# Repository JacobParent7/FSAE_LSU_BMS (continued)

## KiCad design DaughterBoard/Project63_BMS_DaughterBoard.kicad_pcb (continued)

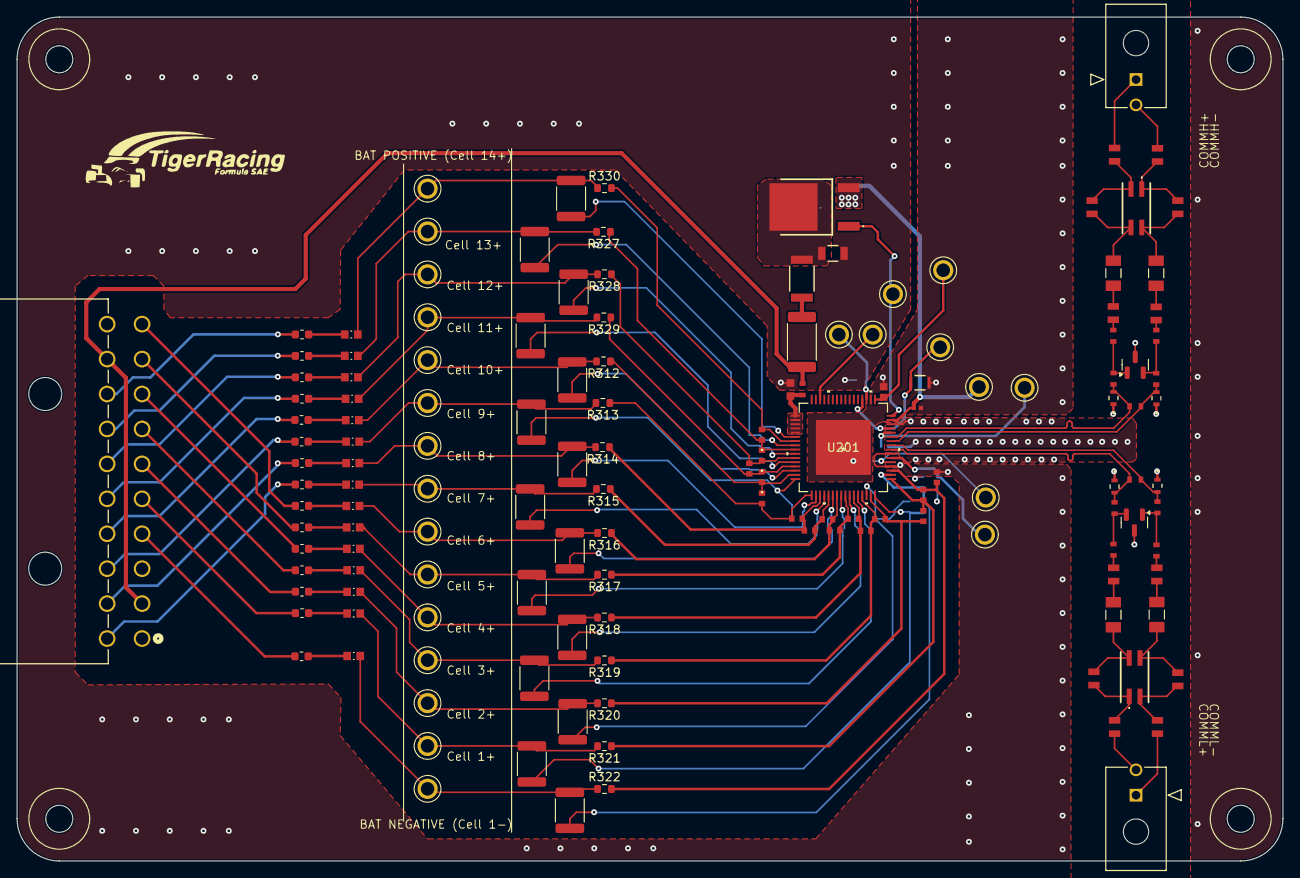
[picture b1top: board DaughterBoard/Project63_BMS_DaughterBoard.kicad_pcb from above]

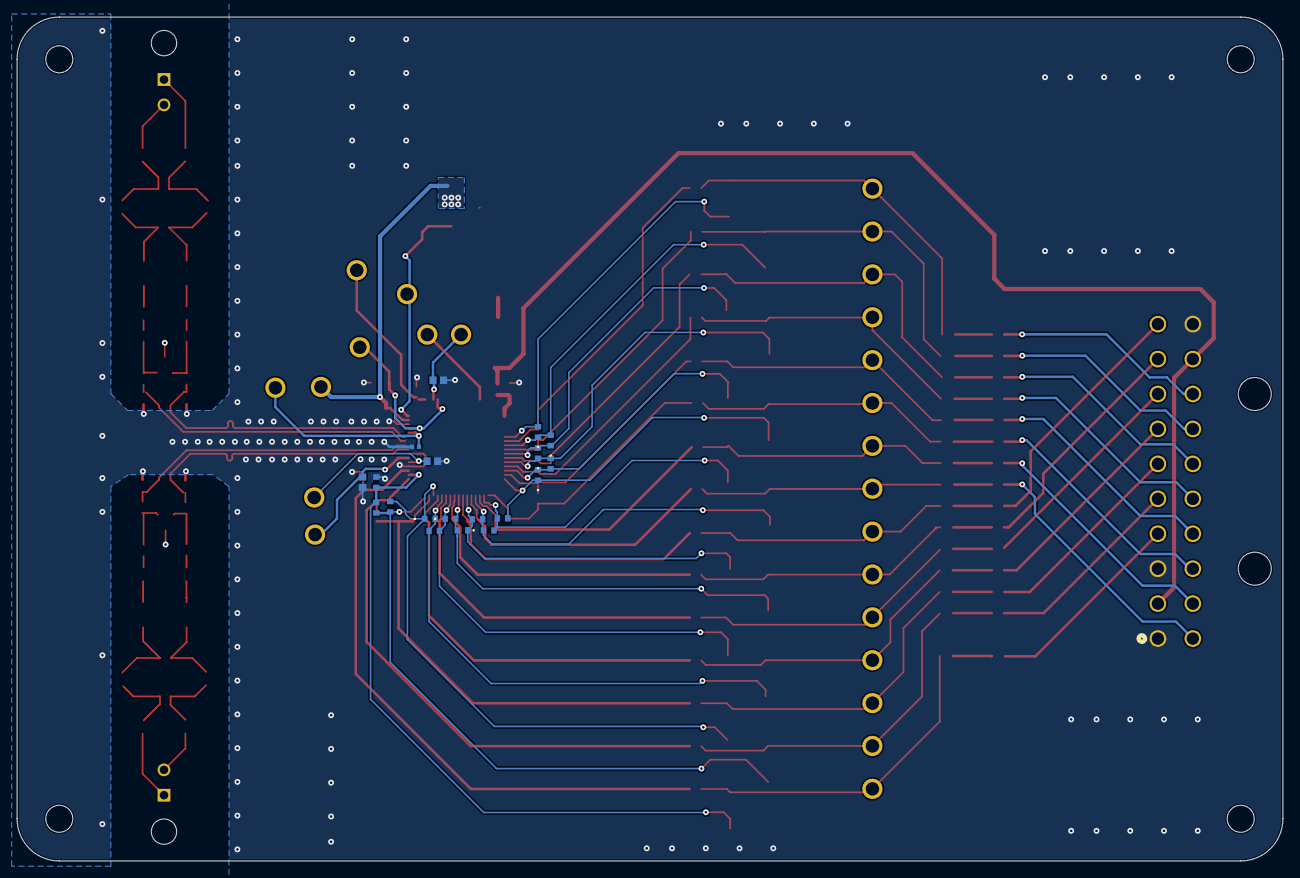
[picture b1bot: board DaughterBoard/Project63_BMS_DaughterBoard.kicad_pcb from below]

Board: 4 copper layers, 150.0 x 100.0 mm, 169 parts (19 on the bottom side), 117 nets.

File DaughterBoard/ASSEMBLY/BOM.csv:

"Reference","Value","Footprint","JLC PCB Part #"
"C201","10nF","GCM188R72A103KA37J:CAPC1608X90N","C2167085"
"C202,C208","0.1uF","GCM155R71A104KA55D:CAP_GCM15_1p05X0p55X0p55_MUR-L","C161163"
"C203,C204,C205,C207","1uF","C0603C105K8RACAUTO:CAPC18095_95N_KEM-L","C29936"
"C206","4.7uF","C2012X7R1A475M125AC:CAP_2012_TDK-L","C277499"
"C301,C302,C303,C304,C305,C306,C307,C308,C309,C310,C311,C312,C313,C314,C315,C316,C317,C318,C319,C320,C321,C322,C323,C324,C325,C326,C327,C328,C329,C330","0.47uF","GCM188R71C474KA55D:G-188_MUR-L","C161214"
"C601","0.22uF","GCM31MR72A224KA37L:G-31_MUR-L","C161277"
"C701,C702,C707,C708","2200pF","1206J2K00222KXR (1):CAPC3216X160N","C107194"
"C703,C704,C705,C706","220pF","CL10B221JB8NNNC:CAP_CL10_SAM-L","C107081"
"D701,D702","24V","Package_TO_SOT_SMD:SOT-23","C314266"
"F301,F302,F303,F304,F305,F306,F307,F308,F309,F310,F311,F323,F324,F325,F326","0438.250WRA","Fuse:Fuse_0603_1608Metric","C151137"
"F312,F313,F314,F315,F316,F317,F318,F319,F320,F321,F322,F327,F328,F329,F330","0686F1000-01","0686F1000-01:FUSC1608X60N","C136329"
"FL701,FL702","470uH","KiCad:744242471","C488250"
"Q601","ZXTN4004KTC","ZXTN4004KTC:ZXTN4004KTC","C157603"
"R201","30","ERJ-3EKF30R0V:RC0603N_PAN-L","C403150"
"R301,R302,R303,R304,R305,R306,R307,R308,R309,R310,R311,R323,R324,R325,R326","7.5","Resistor_SMD:R_1812_4532Metric","C5204035"
"R312,R313,R314,R315,R316,R317,R318,R319,R320,R321,R322,R327,R328,R329,R330","100","Resistor_SMD:R_0603_1608Metric","C5123580"
"R601","100","CRCW2010100RFKEF:RES_CRCW_2010-L","C305269"
"R602","200","Resistor_SMD:R_2512_6332Metric","C2935248"
"R701,R702,R705,R706,R709,R710,R713,R714,R715,R716,R721,R722","0","CRCW08050000Z0EAHP:RES_CRCW_0805_VIS-L","C844811"
"R703,R704,R719,R720","0","RC0603JR-070RL:RC0603N_YAG-L","C95177"
"R707,R708,R717,R718","51","CRCW060351R0JNEA:RC0603N_VIS-L","C844178"
"R711,R712","1k","ERJ-3EKF1001V:RC0603N_PAN-L","C2907002"
"U201","BQ79614PAPRQ1","BQ79614:QFP_4PAPRQ1_TEX-L","C3682338"

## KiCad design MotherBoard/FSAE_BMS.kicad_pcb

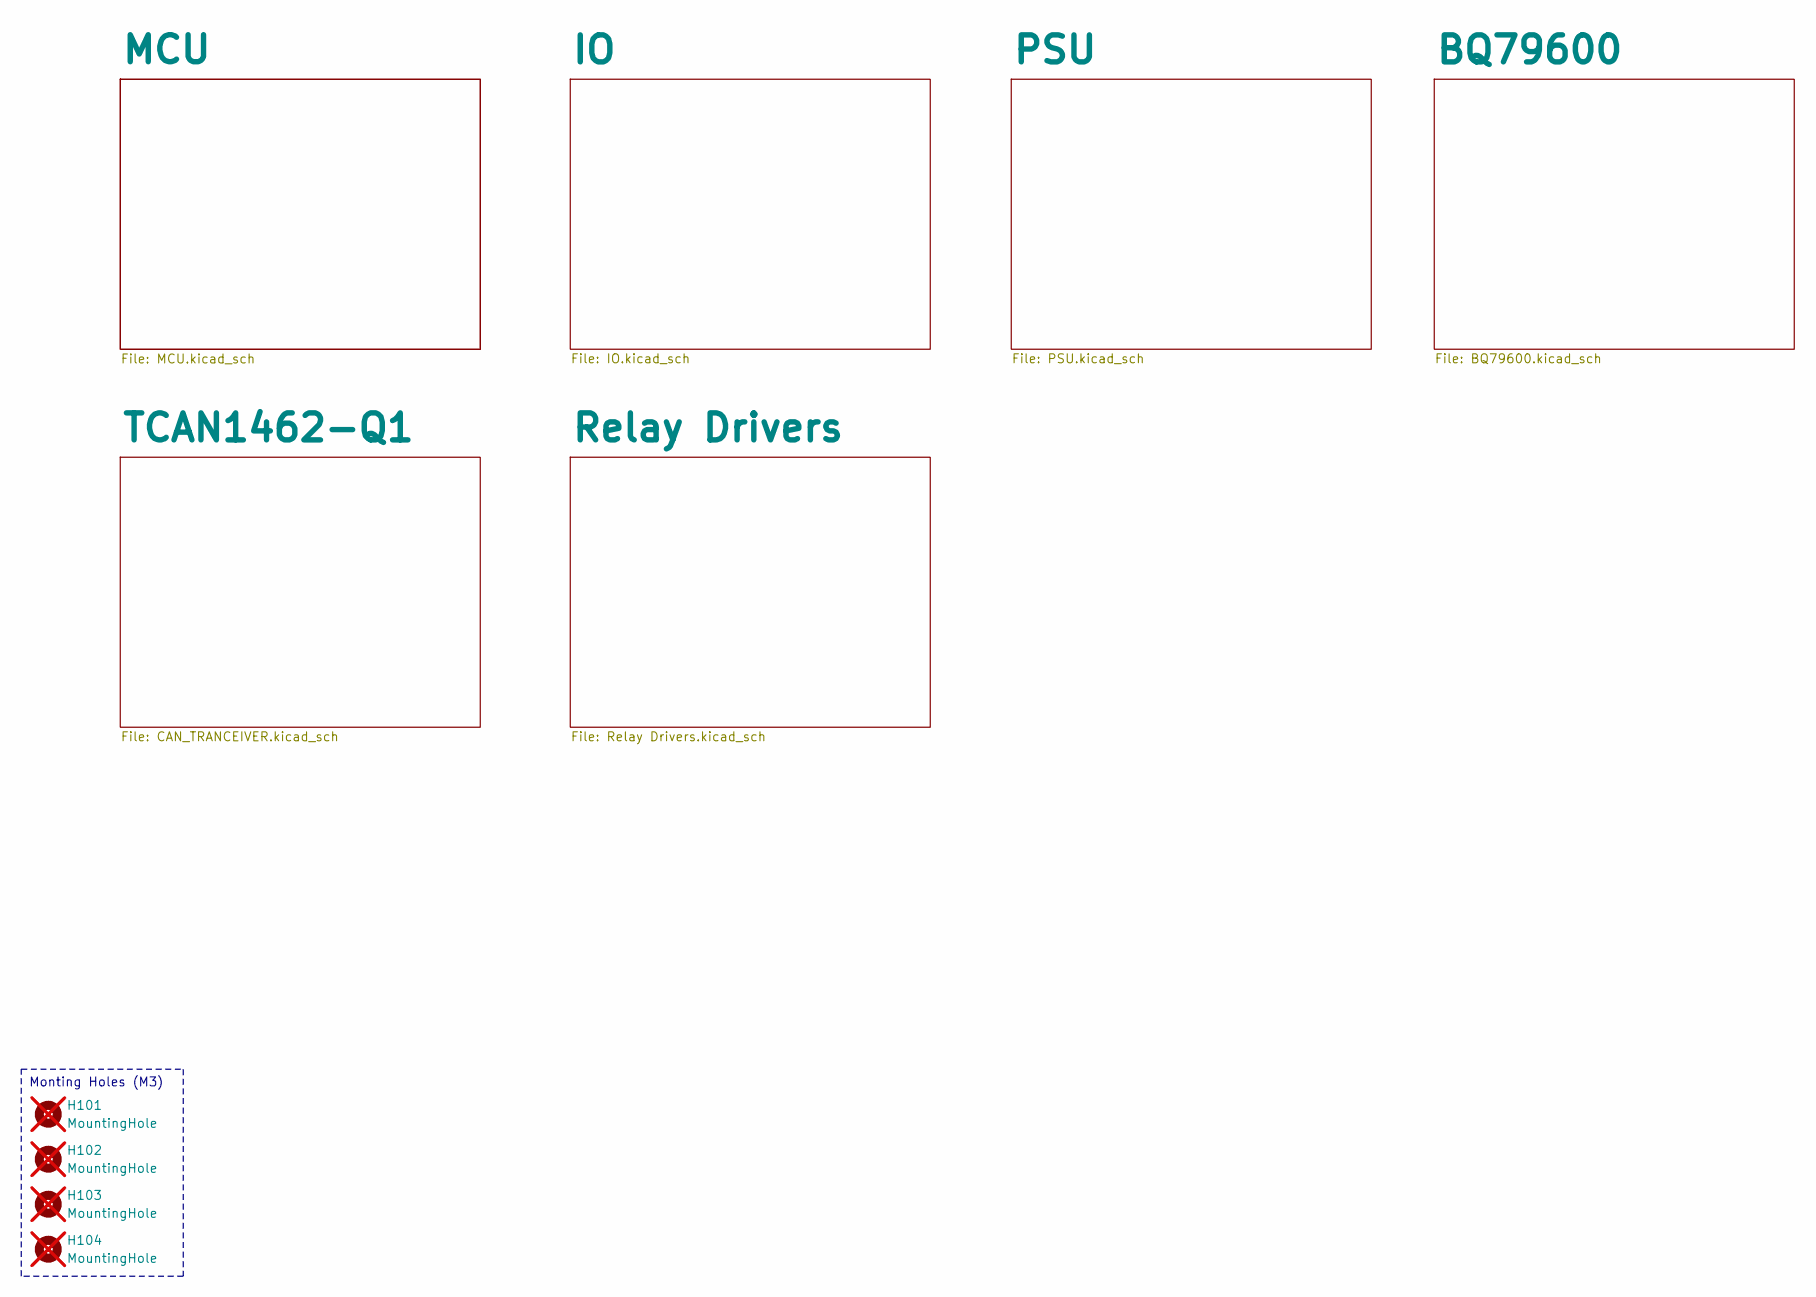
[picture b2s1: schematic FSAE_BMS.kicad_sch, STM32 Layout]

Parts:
H101, H102, H103, H104: MountingHole; MountingHole_3.2mm_M3; not fitted

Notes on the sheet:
Monting Holes (M3)

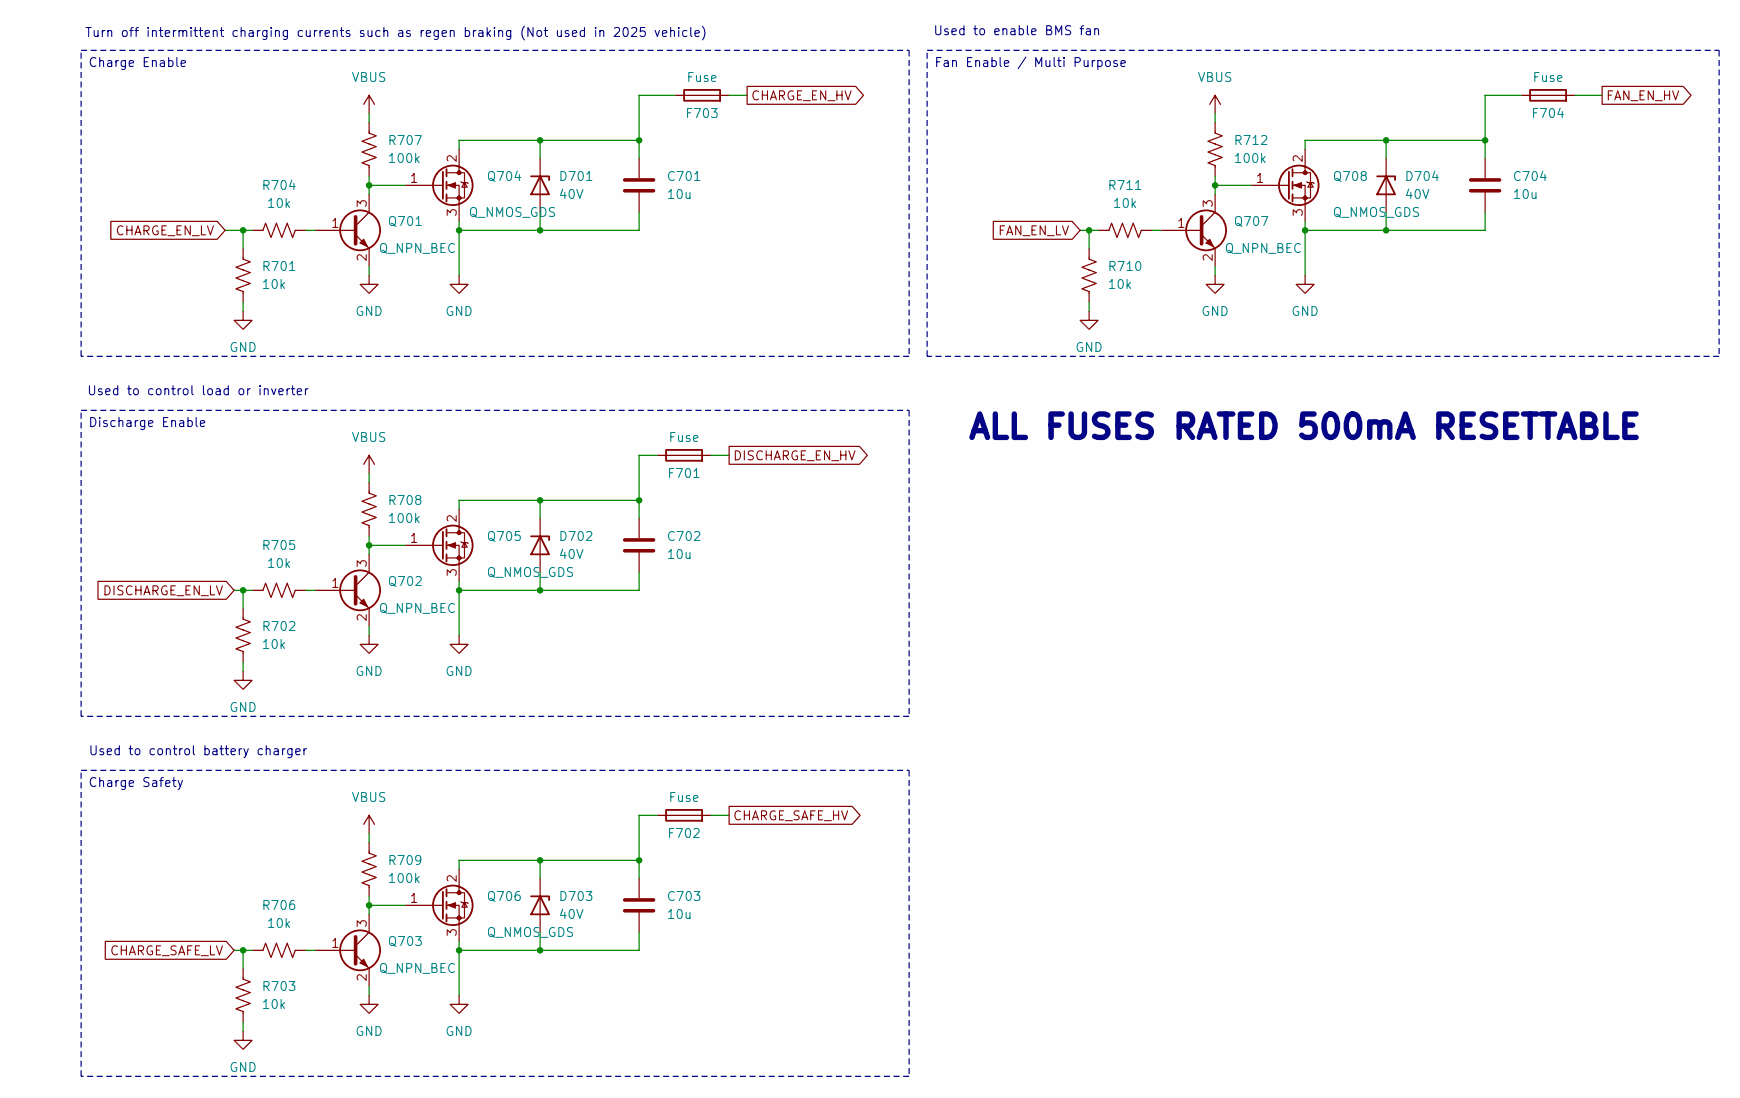
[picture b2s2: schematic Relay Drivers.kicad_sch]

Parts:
C701, C702, C703, C704: 10u; C_1206_3216Metric; Manufacturer_Part_Number CL31A106KBHNNNE; JLCPCB Part # C13585
D701, D702, D703, D704: 40V; D_SOD-123; Manufacturer_Part_Number BZT52C30; JLCPCB Part # C19077418
F701, F702, F703, F704: Fuse; Fuse_1812_4532Metric; Manufacturer_Part_Number SMD1812P050TF/30; JLCPCB Part # C12559
Q701, Q702, Q703, Q707: Q_NPN_BEC; SOT-23; Manufacturer_Part_Number MMBT3904; JLCPCB Part # C7420353
Q704, Q705, Q706, Q708: Q_NMOS_GDS; TO-263-2; Manufacturer_Part_Number IRF3205STRLPBF; JLCPCB Part # C2613
R701, R702, R703, R704, R705, R706, R710, R711: 10k; R_0402_1005Metric; Manufacturer_Part_Number FRC0603J103TS; JLCPCB Part # C2930027
R707, R708, R709, R712: 100k; R_0402_1005Metric; Manufacturer_Part_Number 0402WGF1003TCE; JLCPCB Part # C25741

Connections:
CHARGE_EN_HV: F703.2; also elsewhere on the board
CHARGE_EN_LV: R701.2, R704.1; also elsewhere on the board
CHARGE_SAFE_HV: F702.2; also elsewhere on the board
CHARGE_SAFE_LV: R703.2, R706.1; also elsewhere on the board
DISCHARGE_EN_HV: F701.2; also elsewhere on the board
DISCHARGE_EN_LV: R702.2, R705.1; also elsewhere on the board
FAN_EN_HV: F704.2; also elsewhere on the board
FAN_EN_LV: R710.2, R711.1; also elsewhere on the board
GND: C701.2, C702.2, C703.2, C704.2, D701.2 (A), D702.2 (A), D703.2 (A), D704.2 (A), Q701.2 (E), Q702.2 (E), Q703.2 (E), Q704.3 (S), Q705.3 (S), Q706.3 (S), Q707.2 (E), Q708.3 (S), R701.1, R702.1, R703.1, R710.1; also elsewhere on the board
unnamed: C701.1, D701.1 (K), F703.1, Q704.2 (D)
unnamed: C702.1, D702.1 (K), F701.1, Q705.2 (D)
unnamed: C703.1, D703.1 (K), F702.1, Q706.2 (D)
unnamed: C704.1, D704.1 (K), F704.1, Q708.2 (D)
unnamed: Q701.1 (B), R704.2
unnamed: Q701.3 (C), Q704.1 (G), R707.2
unnamed: Q702.1 (B), R705.2
unnamed: Q702.3 (C), Q705.1 (G), R708.2
unnamed: Q703.1 (B), R706.2
unnamed: Q703.3 (C), Q706.1 (G), R709.2
unnamed: Q707.1 (B), R711.2
unnamed: Q707.3 (C), Q708.1 (G), R712.2
VBUS: R707.1, R708.1, R709.1, R712.1; also elsewhere on the board

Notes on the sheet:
Turn off intermittent charging currents such as regen braking (Not used in 2025 vehicle)
Used to control load or inverter
ALL FUSES RATED 500mA RESETTABLE
Used to control battery charger
Used to enable BMS fan
Charge Safety
Fan Enable / Multi Purpose
Discharge Enable
Charge Enable

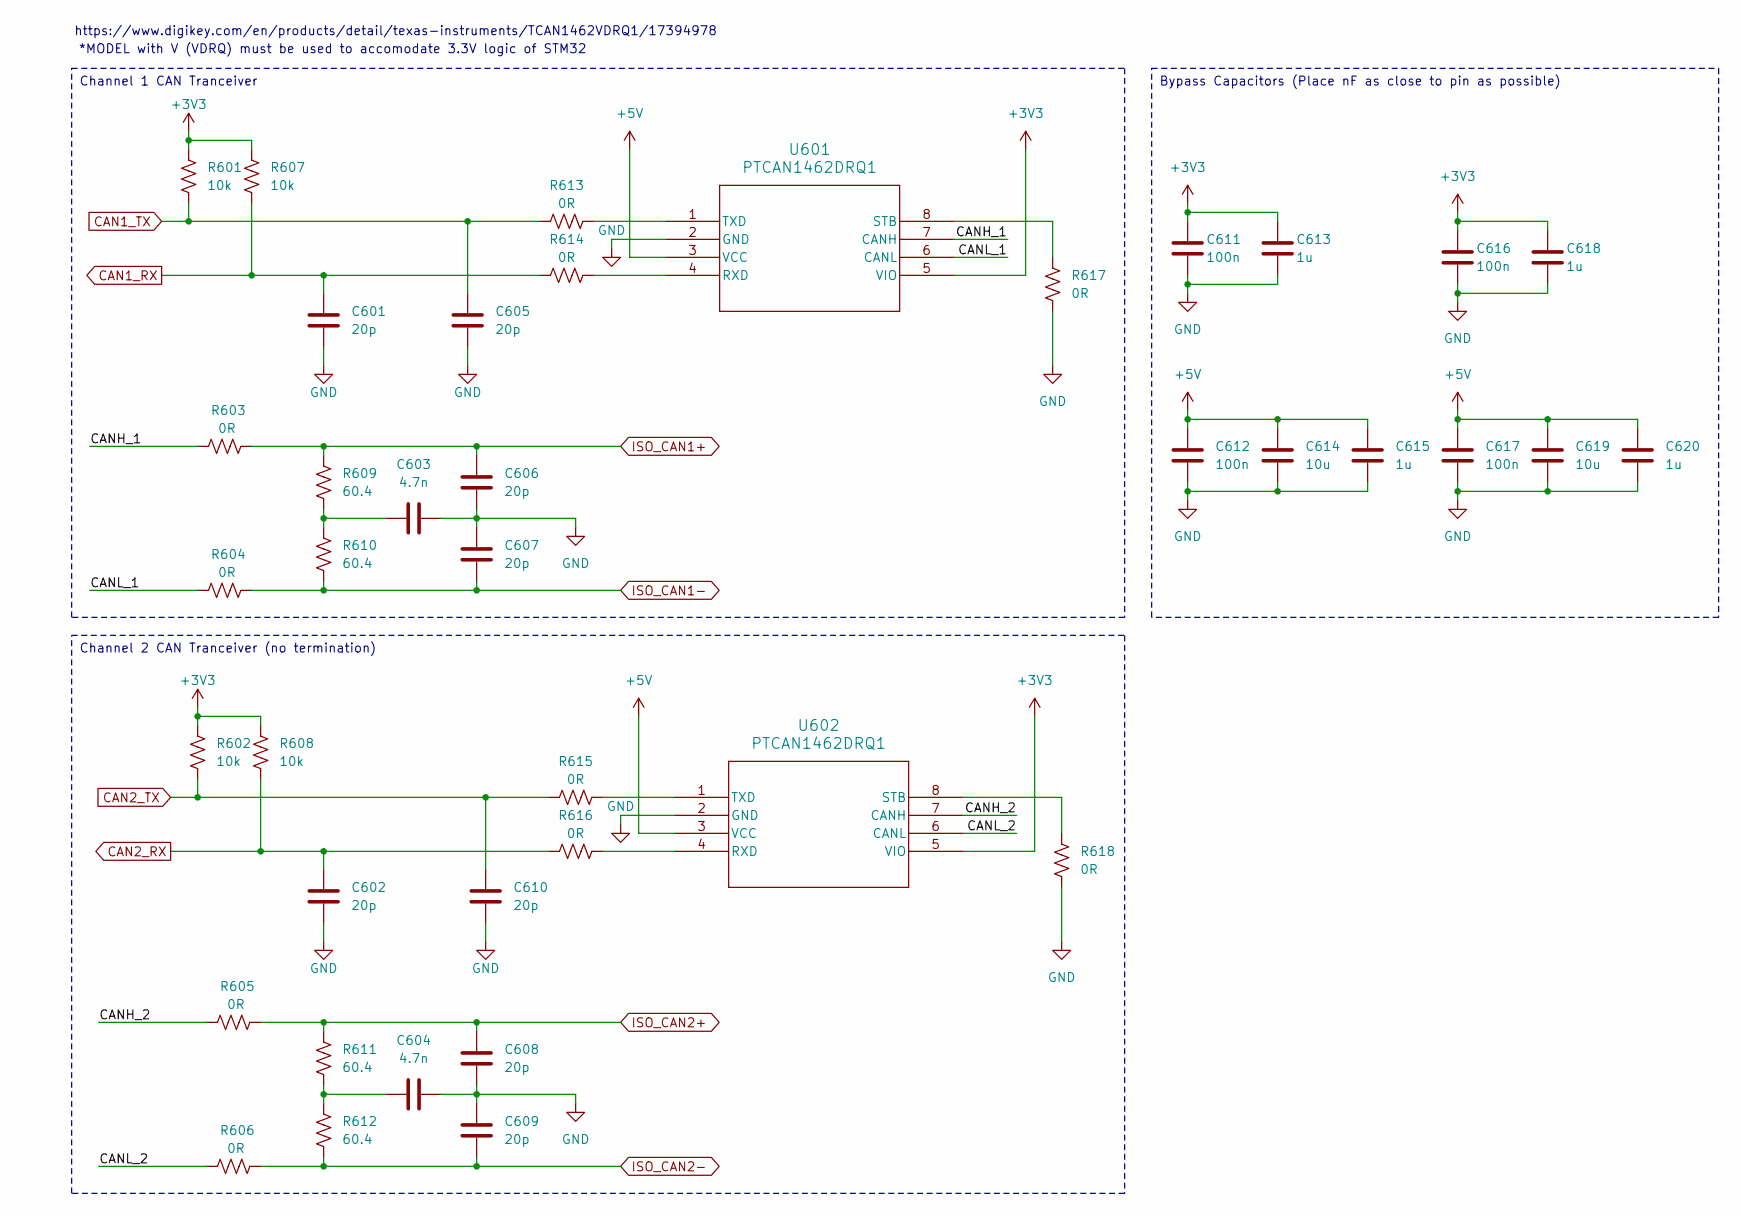
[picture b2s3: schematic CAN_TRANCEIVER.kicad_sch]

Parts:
C601, C602, C605, C606, C607, C608, C609, C610: 20p; C_0402_1005Metric; Manufacturer_Part_Number 0402CG200J500NT; JLCPCB Part # C1554
C603, C604: 4.7n; C_0402_1005Metric; Manufacturer_Part_Number CC0402JRX7R9BB472; JLCPCB Part # C281757
C611, C612, C616, C617: 100n; C_0402_1005Metric; Manufacturer_Part_Number CL05B104KO5NNNC; JLCPCB Part # C1525
C613, C615, C618, C620: 1u; C_0402_1005Metric; Manufacturer_Part_Number CL05A105KO5NNNC; JLCPCB Part # C29266
C614, C619: 10u; C_0603_1608Metric; Manufacturer_Part_Number CL10A106KP8NNNC; JLCPCB Part # C19702
R601, R602, R607, R608: 10k; R_0402_1005Metric; Manufacturer_Part_Number FRC0603J103TS; JLCPCB Part # C2930027
R603, R604, R605, R606: 0R; R_1206_3216Metric; Manufacturer_Part_Number HP06W2J0000T5E; JLCPCB Part # C473612
R609, R610, R611, R612: 60.4; R_1210_3225Metric; Manufacturer_Part_Number AC1210FR-0760R4L; JLCPCB Part # C230306
R613, R614, R615, R616, R617, R618: 0R; R_0805_2012Metric; Manufacturer_Part_Number 0805W8F0000T5E; JLCPCB Part # C17477
U601, U602: PTCAN1462DRQ1; CAN1462; Manufacturer_Part_Number TCAN1462VDRQ1; JLCPCB Part # C7399456

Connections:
+3V3: C611.1, C613.1, C616.1, C618.1, R601.1, R602.1, R607.1, R608.1, U601.5 (VIO), U602.5 (VIO); also elsewhere on the board
+5V: C612.1, C614.1, C615.1, C617.1, C619.1, C620.1, U601.3 (VCC), U602.3 (VCC); also elsewhere on the board
/TCAN1462-Q1/CANH_1: R603.1, U601.7 (CANH)
/TCAN1462-Q1/CANH_2: R605.1, U602.7 (CANH)
/TCAN1462-Q1/CANL_1: R604.1, U601.6 (CANL)
/TCAN1462-Q1/CANL_2: R606.1, U602.6 (CANL)
CAN1_RX: C601.2, R607.2, R614.1; also elsewhere on the board
CAN1_TX: C605.2, R601.2, R613.1; also elsewhere on the board
CAN2_RX: C602.2, R608.2, R616.1; also elsewhere on the board
CAN2_TX: C610.2, R602.2, R615.1; also elsewhere on the board
GND: C601.1, C602.1, C603.2, C604.2, C605.1, C606.1, C607.2, C608.1, C609.2, C610.1, C611.2, C612.2, C613.2, C614.2, C615.2, C616.2, C617.2, C618.2, C619.2, C620.2, R617.2, R618.2, U601.2 (GND), U602.2 (GND); also elsewhere on the board
ISO_CAN1+: C606.2, R603.2, R609.2; also elsewhere on the board
ISO_CAN1-: C607.1, R604.2, R610.1; also elsewhere on the board
ISO_CAN2+: C608.2, R605.2, R611.2; also elsewhere on the board
ISO_CAN2-: C609.1, R606.2, R612.1; also elsewhere on the board
unnamed: C603.1, R609.1, R610.2
unnamed: C604.1, R611.1, R612.2
unnamed: R614.2, U601.4 (RXD)
unnamed: R617.1, U601.8 (STB)
unnamed: R613.2, U601.1 (TXD)
unnamed: R616.2, U602.4 (RXD)
unnamed: R618.1, U602.8 (STB)
unnamed: R615.2, U602.1 (TXD)

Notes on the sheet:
Channel 2 CAN Tranceiver (no termination)
Channel 1 CAN Tranceiver
Bypass Capacitors (Place nF as close to pin as possible)
https://www.digikey.com/en/products/detail/texas-instruments/TCAN1462VDRQ1/17394978
*MODEL with V (VDRQ) must be used to accomodate 3.3V logic of STM32

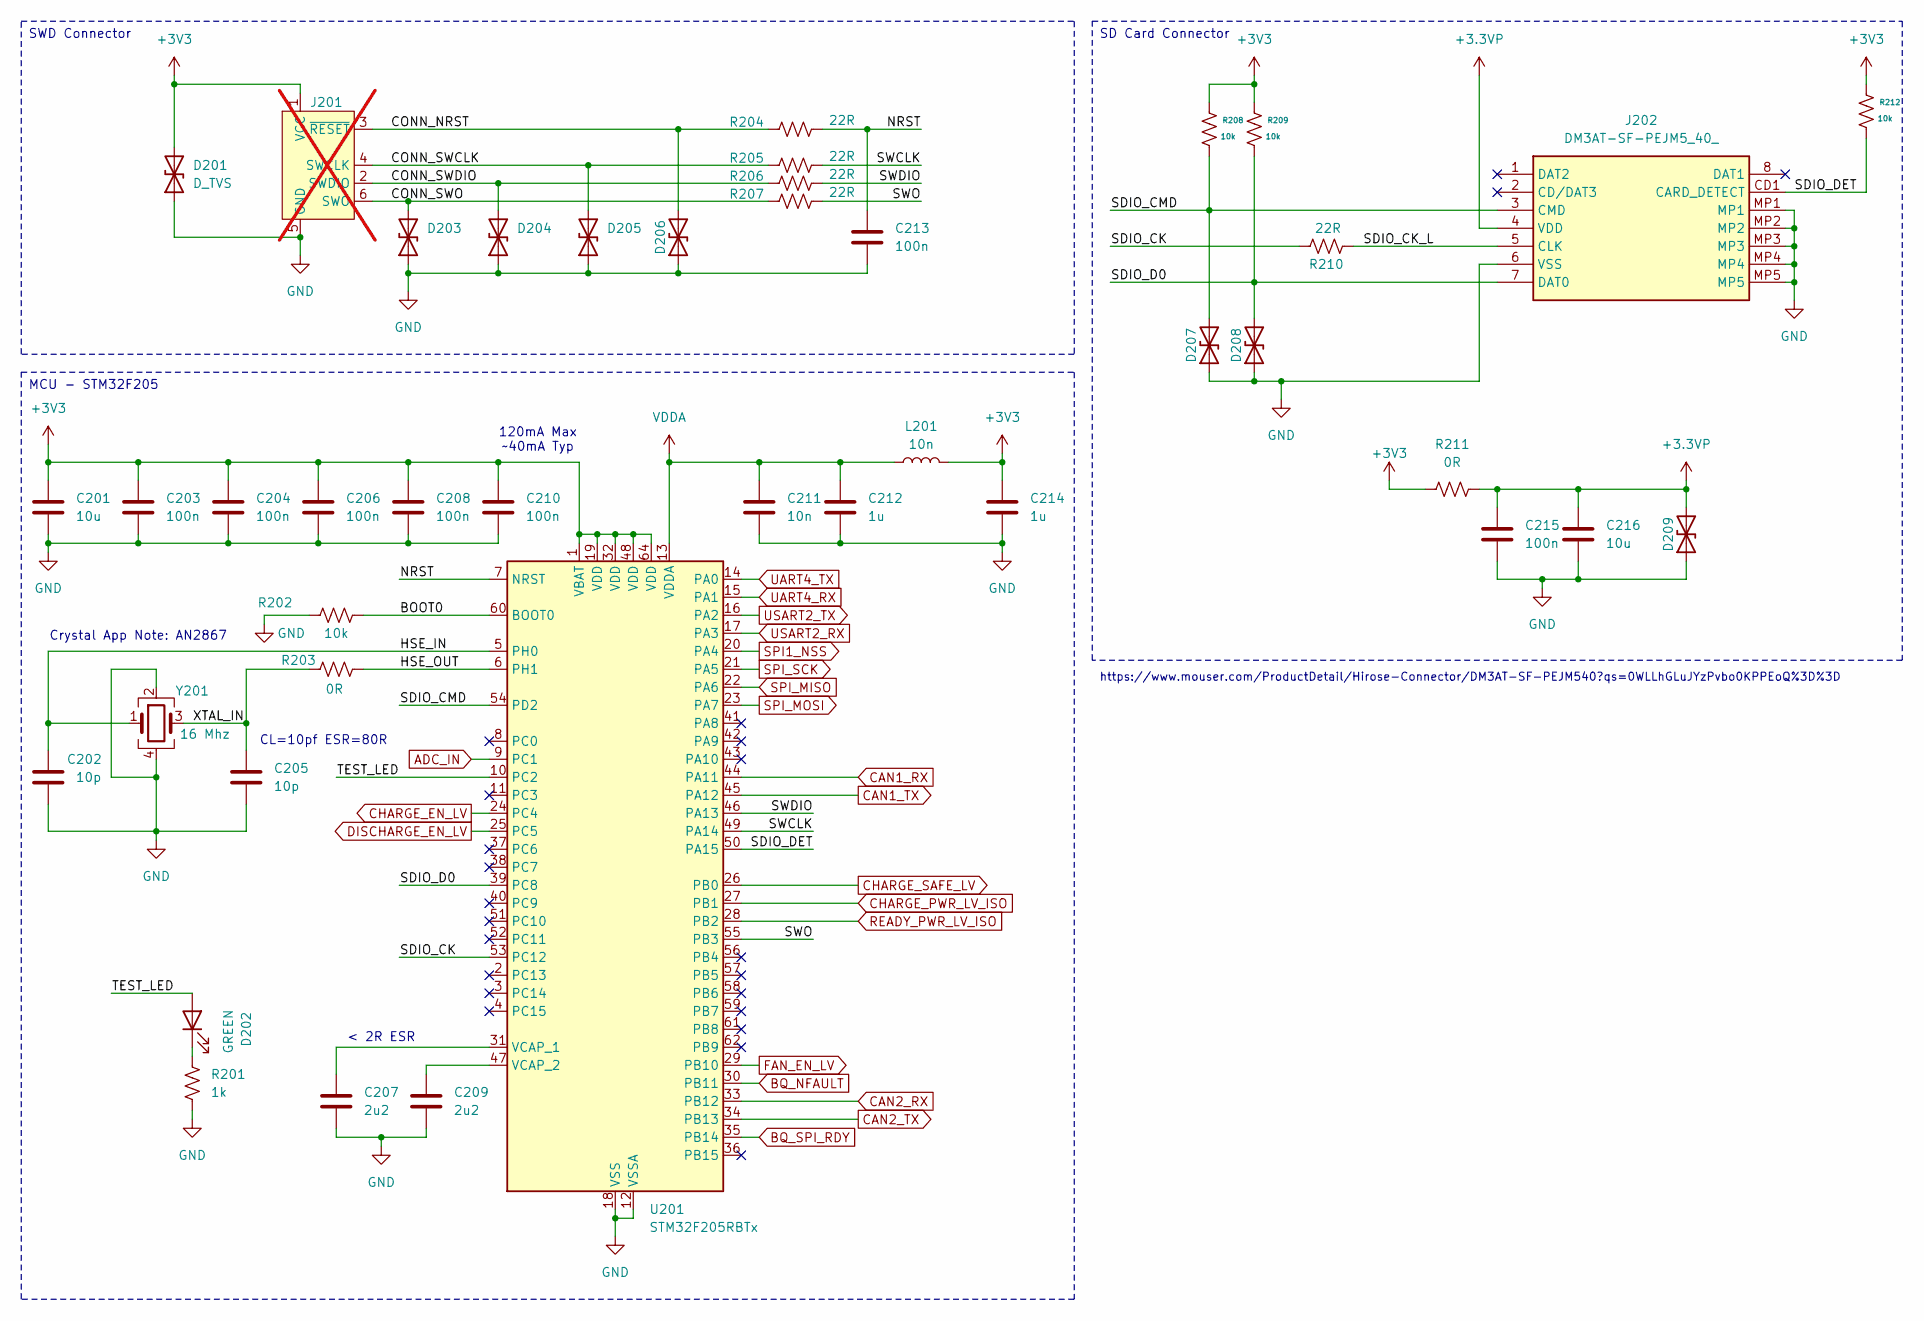
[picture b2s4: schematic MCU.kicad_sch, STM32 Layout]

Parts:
C201, C216: 10u; C_0603_1608Metric; Manufacturer_Part_Number CL10A106KP8NNNC; JLCPCB Part # C19702
C202, C205: 10p; C_0402_1005Metric; Manufacturer_Part_Number GRM1555C1H100FA01D; JLCPCB Part # C161520
C203, C204, C206, C208, C210, C213, C215: 100n; C_0402_1005Metric; Manufacturer_Part_Number CL05B104KO5NNNC; JLCPCB Part # C1525
C207, C209: 2u2; C_0603_1608Metric; Manufacturer_Part_Number 0603B225K250NT; JLCPCB Part # C99228
C211: 10n; C_0402_1005Metric; Manufacturer_Part_Number CC0402KRX7R9BB103; JLCPCB Part # C60133
C212, C214: 1u; C_0402_1005Metric; Manufacturer_Part_Number CL05A105KO5NNNC; JLCPCB Part # C29266
D201, D203, D204, D205, D206, D207, D208, D209: D_TVS; D_SOD-323; Manufacturer_Part_Number PESD3V3L1BA,115; JLCPCB Part # C51450
D202: GREEN; LED_0603_1608Metric; Manufacturer_Part_Number VLMTG1401-GS08; JLCPCB Part # C511604
J201: Conn_ARM_SWD_TagConnect_TC2030; Tag-Connect_TC2030-IDC-FP_2x03_P1.27mm_Vertical; not fitted
J202: DM3AT-SF-PEJM5_40_; SD_CARD; Mouser Part Number 798-DM3AT-SF-PEJM540
L201: 10n; L_0402_1005Metric; Manufacturer_Part_Number LQG15HN10NJ02D; JLCPCB Part # C21585
R201: 1k; R_0402_1005Metric; Manufacturer_Part_Number 0402WGF1001TCE; JLCPCB Part # C11702
R202, R208, R209, R212: 10k; R_0402_1005Metric; Manufacturer_Part_Number FRC0603J103TS; JLCPCB Part # C2930027
R203: 0R; R_0402_1005Metric; Manufacturer_Part_Number 0402WGF0000TCE; JLCPCB Part # C17168
R204, R205, R206, R207, R210: 22R; R_0402_1005Metric; Manufacturer_Part_Number 0402WGF220JTCE; JLCPCB Part # C25092
R211: 0R; R_2512_6332Metric; Manufacturer_Part_Number 25121WJ0000T4E; JLCPCB Part # C25469
U201: STM32F205RBTx; LQFP-64_10x10mm_P0.5mm; Manufacturer_Part_Number STM32F205RBT6; JLCPCB Part # C8364
Y201: 16 Mhz; Crystal_SMD_3225-4Pin_3.2x2.5mm; Manufacturer_Part_Number X322516MLB4SI; JLCPCB Part # C13738

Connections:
+3.3VP: C215.1, C216.1, D209.2 (A2), J202.4 (VDD), R211.2
+3V3: C201.1, C203.1, C204.1, C206.1, C208.1, C210.1, C214.1, D201.2 (A2), J201.1 (VCC), L201.2, R208.1, R209.1, R211.1, R212.1, U201.1 (VBAT), U201.19 (VDD), U201.32 (VDD), U201.48 (VDD), U201.64 (VDD); also elsewhere on the board
/MCU/BOOT0: R202.1, U201.60 (BOOT0)
/MCU/CONN_NRST: D206.2 (A2), J201.3 (~RESET), R204.1
/MCU/CONN_SWCLK: D205.2 (A2), J201.4 (SWCLK), R205.1
/MCU/CONN_SWDIO: D204.2 (A2), J201.2 (SWDIO), R206.1
/MCU/CONN_SWO: D203.2 (A2), J201.6 (SWO), R207.1
/MCU/HSE_IN: C202.1, U201.5 (PH0), Y201.1
/MCU/HSE_OUT: R203.2, U201.6 (PH1)
/MCU/NRST: C213.1, R204.2, U201.7 (NRST)
/MCU/SDIO_CK: R210.1, U201.53 (PC12)
/MCU/SDIO_CK_L: J202.5 (CLK), R210.2
/MCU/SDIO_CMD: D207.2 (A2), J202.3 (CMD), R208.2, U201.54 (PD2)
/MCU/SDIO_D0: D208.2 (A2), J202.7 (DAT0), R209.2, U201.39 (PC8)
/MCU/SDIO_DET: J202.CD1 (CARD_DETECT), R212.2, U201.50 (PA15)
/MCU/SWCLK: R205.2, U201.49 (PA14)
/MCU/SWDIO: R206.2, U201.46 (PA13)
/MCU/SWO: R207.2, U201.55 (PB3)
/MCU/TEST_LED: D202.2 (A), U201.10 (PC2)
/MCU/XTAL_IN: C205.1, R203.1, Y201.3
ADC_IN: U201.9 (PC1); also elsewhere on the board
BQ_NFAULT: U201.30 (PB11); also elsewhere on the board
BQ_SPI_RDY: U201.35 (PB14); also elsewhere on the board
CAN1_RX: U201.44 (PA11); also elsewhere on the board
CAN1_TX: U201.45 (PA12); also elsewhere on the board
CAN2_RX: U201.33 (PB12); also elsewhere on the board
CAN2_TX: U201.34 (PB13); also elsewhere on the board
CHARGE_EN_LV: U201.24 (PC4); also elsewhere on the board
CHARGE_PWR_LV_ISO: U201.27 (PB1); also elsewhere on the board
CHARGE_SAFE_LV: U201.26 (PB0); also elsewhere on the board
DISCHARGE_EN_LV: U201.25 (PC5); also elsewhere on the board
FAN_EN_LV: U201.29 (PB10); also elsewhere on the board
GND: C201.2, C202.2, C203.2, C204.2, C205.2, C206.2, C207.2, C208.2, C209.2, C210.2, C211.2, C212.2, C213.2, C214.2, C215.2, C216.2, D201.1 (A1), D203.1 (A1), D204.1 (A1), D205.1 (A1), D206.1 (A1), D207.1 (A1), D208.1 (A1), D209.1 (A1), J201.5 (GND), J202.6 (VSS), J202.MP1, J202.MP2, J202.MP3, J202.MP4, J202.MP5, R201.2, R202.2, U201.12 (VSSA), U201.18 (VSS), U201.63 (VSS), Y201.2, Y201.4; also elsewhere on the board
unnamed: D202.1 (K), R201.1
unnamed: C207.1, U201.31 (VCAP_1)
unnamed: C209.1, U201.47 (VCAP_2)
READY_PWR_LV_ISO: U201.28 (PB2); also elsewhere on the board
SPI1_NSS: U201.20 (PA4); also elsewhere on the board
SPI_MISO: U201.22 (PA6); also elsewhere on the board
SPI_MOSI: U201.23 (PA7); also elsewhere on the board
SPI_SCK: U201.21 (PA5); also elsewhere on the board
UART4_RX: U201.15 (PA1); also elsewhere on the board
UART4_TX: U201.14 (PA0); also elsewhere on the board
USART2_RX: U201.17 (PA3); also elsewhere on the board
USART2_TX: U201.16 (PA2); also elsewhere on the board
VDDA: C211.1, C212.1, L201.1, U201.13 (VDDA)

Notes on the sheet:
Crystal App Note: AN2867
https://www.mouser.com/ProductDetail/Hirose-Connector/DM3AT-SF-PEJM540?qs=0WLLhGLuJYzPvbo0KPPEoQ%3D%3D
120mA Max ~40mA Typ
< 2R ESR
CL=10pf ESR=80R
SD Card Connector
MCU - STM32F205
SWD Connector

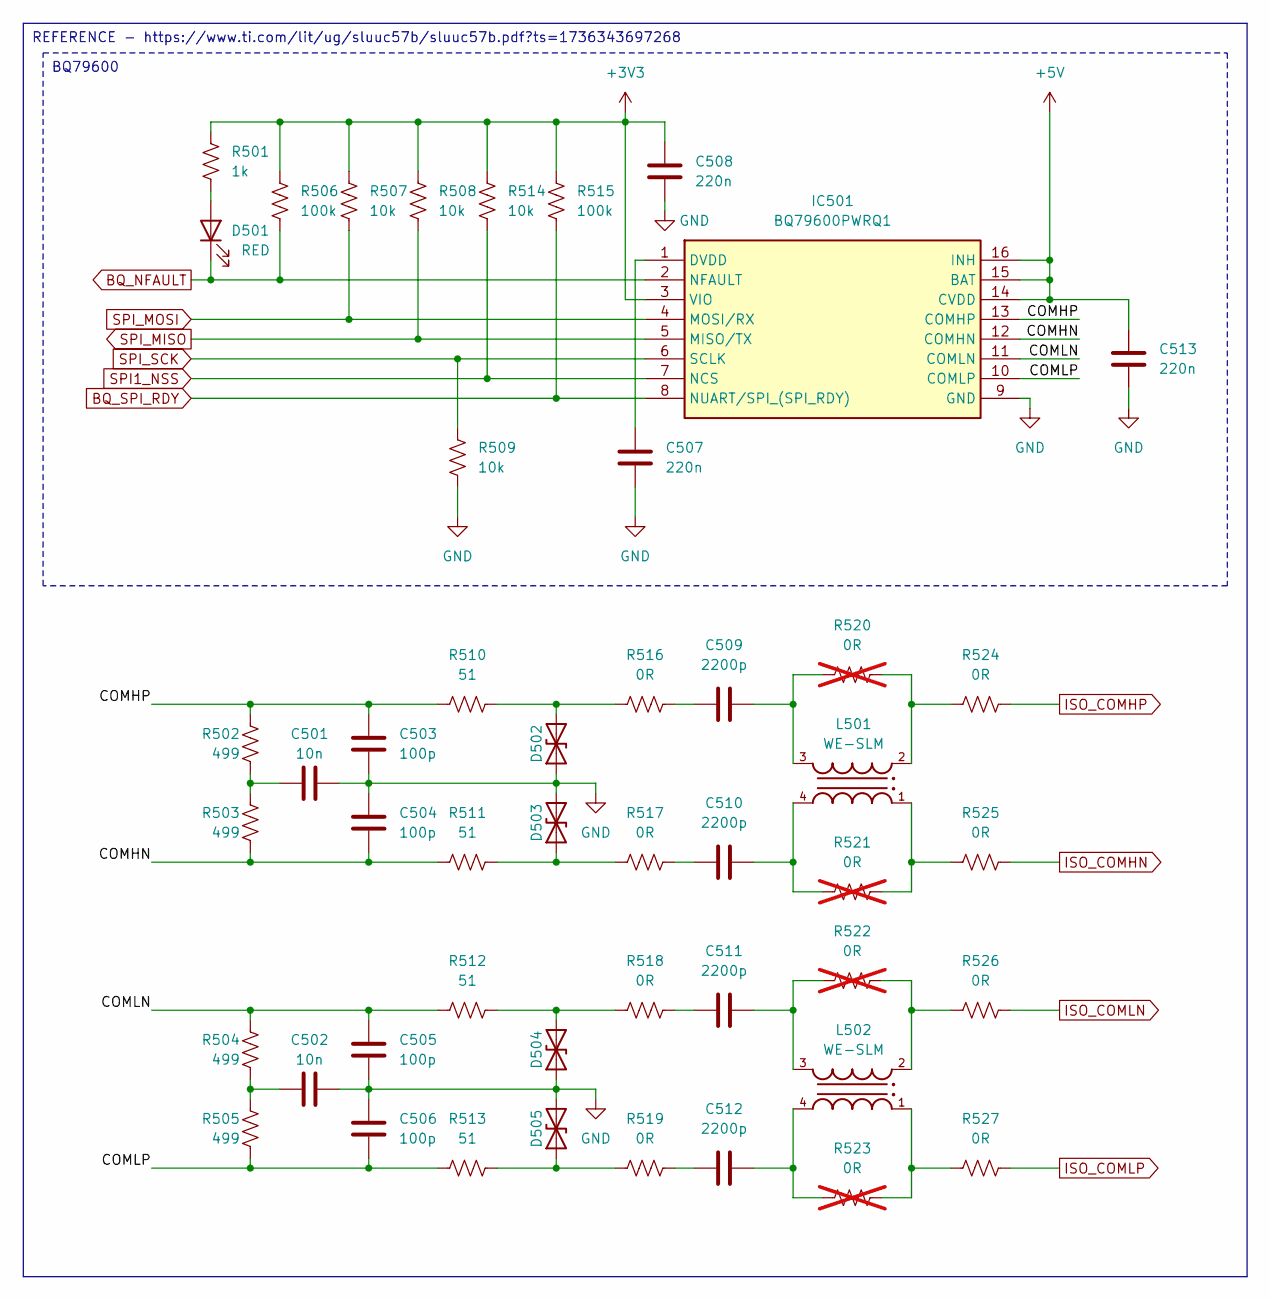
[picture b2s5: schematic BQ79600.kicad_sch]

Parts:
C501, C502: 10n; C_0402_1005Metric; Manufacturer_Part_Number CC0402KRX7R9BB103; JLCPCB Part # C60133
C503, C504, C505, C506: 100p; C_0402_1005Metric; Manufacturer_Part_Number 0402CG101J500NT; JLCPCB Part # C1546
C507, C513: 220n; C_0603_1608Metric; Manufacturer_Part_Number CL10B224KA8NNNC; JLCPCB Part # C21120
C508: 220n; C_0402_1005Metric; Manufacturer_Part_Number CL05A224KA5NNNC; JLCPCB Part # C47129
C509, C510, C511, C512: 2200p; C_0805_2012Metric; Manufacturer_Part_Number CL21C222JBFNNNE; JLCPCB Part # C28260
D501: RED; LED_0603_1608Metric; Manufacturer_Part_Number KT-0603R; JLCPCB Part # C2286
D502, D503, D504, D505: D_TVS; D_SOD-323; Manufacturer_Part_Number ESD5V0D3B-TP; JLCPCB Part # C668923
IC501: BQ79600PWRQ1; BQ79600; Mouser Part Number 595-BQ79600PWRQ1
L501, L502: WE-SLM; Manufacturer_Part_Number 744242471; JLCPCB Part # C488250
R501: 1k; R_0402_1005Metric; Manufacturer_Part_Number 0402WGF1001TCE; JLCPCB Part # C11702
R502, R503, R504, R505: 499; R_0603_1608Metric; Manufacturer_Part_Number 0603WAF4990T5E; JLCPCB Part # C23065
R506, R515: 100k; R_0402_1005Metric; Manufacturer_Part_Number 0402WGF1003TCE; JLCPCB Part # C25741
R507, R508, R509, R514: 10k; R_0402_1005Metric; Manufacturer_Part_Number FRC0603J103TS; JLCPCB Part # C2930027
R510, R511, R512, R513: 51; R_1206_3216Metric; Manufacturer_Part_Number 1206W4F510JT5E; JLCPCB Part # C18019
R516, R517, R518, R519, R524, R525, R526, R527: 0R; R_0805_2012Metric; Manufacturer_Part_Number 0805W8F0000T5E; JLCPCB Part # C17477
R520, R521, R522, R523: 0R; R_0805_2012Metric; Manufacturer_Part_Number 0805W8F0000T5E; not fitted

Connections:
+3V3: C508.1, IC501.3 (VIO), R501.1, R506.1, R507.1, R508.1, R514.1, R515.1; also elsewhere on the board
+5V: C513.1, IC501.14 (CVDD), IC501.15 (BAT), IC501.16 (INH); also elsewhere on the board
/BQ79600/COMHN: C504.1, IC501.12 (COMHN), R503.2, R511.1
/BQ79600/COMHP: C503.2, IC501.13 (COMHP), R502.1, R510.1
/BQ79600/COMLN: C505.2, IC501.11 (COMLN), R504.1, R512.1
/BQ79600/COMLP: C506.1, IC501.10 (COMLP), R505.2, R513.1
BQ_NFAULT: D501.1 (K), IC501.2 (NFAULT), R506.2; also elsewhere on the board
BQ_SPI_RDY: IC501.8 (NUART/SPI_(SPI_RDY)), R515.2; also elsewhere on the board
GND: C501.1, C502.1, C503.1, C504.2, C505.1, C506.2, C507.1, C508.2, C513.2, D502.1 (A1), D503.2 (A2), D504.1 (A1), D505.2 (A2), IC501.9 (GND), R509.2; also elsewhere on the board
ISO_COMHN: R525.2; also elsewhere on the board
ISO_COMHP: R524.2; also elsewhere on the board
ISO_COMLN: R526.2; also elsewhere on the board
ISO_COMLP: R527.2; also elsewhere on the board
unnamed: C501.2, R502.2, R503.1
unnamed: C502.2, R504.2, R505.1
unnamed: C509.1, L501.3, R520.1
unnamed: C509.2, R516.2
unnamed: C510.1, L501.4, R521.1
unnamed: C510.2, R517.2
unnamed: C511.1, L502.3, R522.1
unnamed: C511.2, R518.2
unnamed: C512.1, L502.4, R523.1
unnamed: C512.2, R519.2
unnamed: D501.2 (A), R501.2
unnamed: D502.2 (A2), R510.2, R516.1
unnamed: D503.1 (A1), R511.2, R517.1
unnamed: D504.2 (A2), R512.2, R518.1
unnamed: D505.1 (A1), R513.2, R519.1
unnamed: C507.2, IC501.1 (DVDD)
unnamed: L501.1, R521.2, R525.1
unnamed: L501.2, R520.2, R524.1
unnamed: L502.1, R523.2, R527.1
unnamed: L502.2, R522.2, R526.1
SPI1_NSS: IC501.7 (NCS), R514.2; also elsewhere on the board
SPI_MISO: IC501.5 (MISO/TX), R508.2; also elsewhere on the board
SPI_MOSI: IC501.4 (MOSI/RX), R507.2; also elsewhere on the board
SPI_SCK: IC501.6 (SCLK), R509.1; also elsewhere on the board

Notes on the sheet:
REFERENCE - https://www.ti.com/lit/ug/sluuc57b/sluuc57b.pdf?ts=1736343697268
BQ79600
